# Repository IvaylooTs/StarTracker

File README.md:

# Repo: Star Tracker

**Team Name:** CASSI  
**Project Name:** CASSI (Celestial Alignment System for Satellite Inertial-control)  
**Official Category:** Star Tracker 1

**Team Members:**  
Michael Yan, Ivaylo Tsekov, Alexandra Nedela, Dilyana Vasileva, Tsvetomir Staykov

## Note: for full and final documentation please read Star_Tracker_3.pdf
---

## Problem

How do we determine our attitude in space?

---

## Project Overview and End Goal

This project implements a star tracking system using a **Raspberry Pi** with an **AI camera** to determine the orientation of the system based on captured star images using a deterministic algorithm. Once calibrated, the system works in tandem with an IMU (Inertial Measurement Unit) to track orientation without continuous visual input. When drifting occurs, due to environmental variables, power loss, or other factors, the system automatically recalibrates.

---

## Current Available Demo

Go to the `digital_twin` folder in the `src` directory. It contains:

- `main.py` – main file with all the systems  
- `star_distances_sorted.db` – database with calculated angular distances, sorted in ascending order  
- `star_identified.png` – sample image from previous tests  
- `test_images` – dir with images from *Stellarium* for testing purposes (uses specific resolution and FOV)
- `create_hash.py` - a script to generate a hash map from database table "AngularDistances"
- `catalog_hash.py` - an already generated hash with the script above using 2 degree tolerance
- `stellarium360_new.js` - a script to be pasted into stellarium console for testing purposes
- `script_images` - dir with images generated from the above script

To run the script, you will need the `sqlite3` and `cv2` libraries installed on your system, and Python 3.

To run the script, use:
```bash
python3 main.py 
```

The results in your terminal should be:

- Indicator of which image you are currently processing
- Which mode you're in (Lost-in-Space / Tracking)
- The resulting quaternion from either of the two modes if one is produced
- The mapping of image star to HIP ID if one is produced

Files that should be generated when you run the script:

- For each image that you're processing you should get a file generated in this format "stars_identified_[index]"

---

## System Architecture

### Software

#### Database Structure

We have two tables in our database.  
**Table 1 – "Stars"** contains the HIP of each star according to the Hipparcos catalog, the magnitude of each star, and x, y, z coordinates of a unit vector corresponding to their RA and DEC coordinates in the equatorial coordinate system.  
**Table 2 – "AngularDistances"** contains the calculated angular distance between each pair of stars in Table 1, sorted from lowest to highest value.

The stars are filtered based on:

- Brightness  
- Size  
- Eccentricity

#### Lost-in-Space Algorithm

We're implementing a Lost-in-Space approach based on pair matching. The algorithm has four main parts:  
1. Image Processing and Feature Extraction  
2. Angular Distance Calculations  
3. Mapping to Catalog  
4. Attitude Determination

---

#### 1. Image Processing and Feature Extraction

The stars in the image are filtered based on: Brightness, Size, and Eccentricity.  
Then we select the N brightest stars in our image using blob detection and the `cv2` Python module. From this, we get the (x, y) coordinates of the center of each star in the image.

---

#### 2. Angular Distance Calculations

- We center the (x, y) coordinates of the stars based on our image's center, then convert them into vectors with the focal length as the coordinate along the z-axis  
- Convert them into unit vectors to reduce unnecessary computation  
- Calculate the angular distance between each pair (using the cosine of the dot product of the two vectors)

---

#### 3. Mapping Stars to Catalog 

- For each pair of stars in our image, we get the candidates ID pairs from our catalog hash
- Then we assign the candidate IDs for each image star based on a voting system
- Afterwards we run a DFS on this graph-like structure to find all possible mappings (even if incomplete)
- In the end we score the solutions we got from the DFS to get the best one

---

#### 4. Attitude Determination 

- From the final mapping of each star to a certain HIP in our database (from step above), we can now retrieve unit vectors from **Table 1**  
- We build the attitude profile matrix from the two sets of image and catalog vectors
- We then build the attitude profile matrix in quaternion form 
- We solve for the eigenvector with the largest eigenvalue which corresponds to our orientation quaternion

---

#### Tracking algorithm

- For tracking we use a previous orientation quaternion to predict where the stars in our previous image are going to be in the next one 
based on a certain amount of euclidian distance threshold this way we can make small and fast corrections to. We use the hungarian algorithm

---

### Hardware

#### Hardware Integration

- The initial orientation determined via camera is stored as a reference  
- The IMU is zeroed at this orientation  
- Subsequent orientation tracking is performed using only the IMU until recalibration is required due to drift

Notes and Ideas:
- A simple way to recalibrate would be to do it periodically  
- For improved accuracy, consider using Kalman filtering

---

#### Mechanical Design

- Modular, layered physical design:
  - Raspberry Pi  
  - IMU module  
  - Camera mounted perpendicular to the Raspberry Pi board  

- 3D CAD models and assembly diagrams are available in the `DOCS/` directory

---

##  Current Progress

### Software

- [x] Define project requirements  
- [x] Find algorithm for identification of stars  
- [x] OpenCV star identification on image  
  - [x] Test model with math on hand  
- [x] Get angular distances between stars  
- [x] Create database of parameters for comparison (star 1 HIP, star 2 HIP, angular distance)  
- [x] Select candidates for possible stars in specific locations  
- [x] Identify the correct stars  
- [x] Orientation in quaternion form
- [x] Testing  

### Hardware

- [x] Configure Raspberry Pi  
- [x] Connect required modules  
  - [x] Camera  
  - [x] IMU (Gyroscope, Accelerometer, Magnetometer)  
- [x] Calibrate IMU at hardware level  
  - [x] Measure drift  
  - [x] Research drift correction  
- [x] Calibrate IMU at software level  
- [x] Add interface for communication with Arduino (I2C is a good candidate)  
- [x] Develop firmware  
  - [x] Auto boot configuration  

### CAD

- [x] Construct simple box for fit testing and basic implementation  
- [x] Build a better box for testing and protection  
- [x] Satellite enclosure with removable modules  
  - [x] Bottom panel  
  - [x] Sliders  
  - [x] Test sliders  
  - [x] Side protection panels  
  - [x] CASSI module  

### Additional

- [x] Testing | Make black box for testing using images on a monitor  
- [x] Visualization | Make control panel  
  - [x] 3D visualization  
  - [x] Live video  
  - [x] OpenCV calculations  
  - [x] Control buttons  
- [x] Check if static IP is needed (just in case)  
- [x] Study commercial star tracker manuals  
- [x] Consider handling edge cases such as solar flares, moonlight, sun/earth stray light, etc.

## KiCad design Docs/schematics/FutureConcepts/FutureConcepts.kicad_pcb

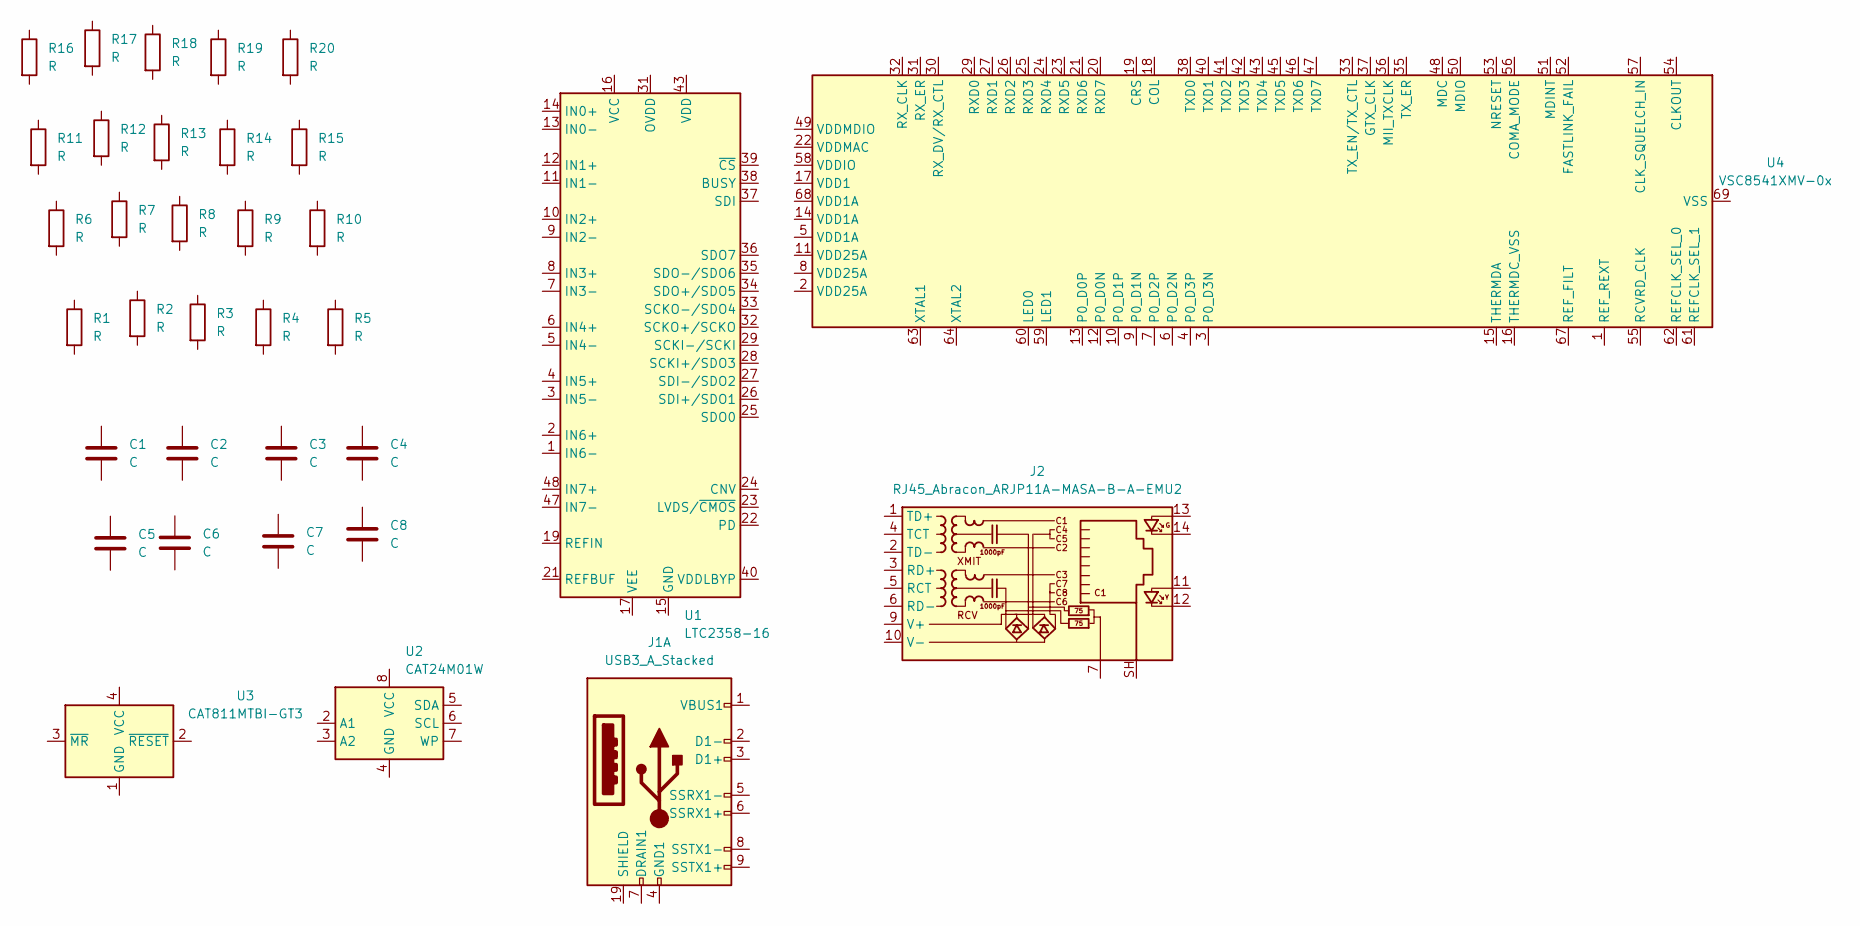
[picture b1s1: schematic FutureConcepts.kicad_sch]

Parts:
C1, C2, C3, C4, C5, C6, C7, C8: C; C_Elec_6.3x5.4
J1: USB3_A_Stacked; USB3_A_Molex_48406-0001_Horizontal_Stacked
J2: RJ45_Abracon_ARJP11A-MASA-B-A-EMU2; RJ45_Abracon_ARJP11A-MA_Horizontal
R1, R2, R3, R4, R5, R6, R7, R8, R9, R10, R11, R12, R13, R14, R15, R16, R17, R18, R19, R20: R; R_2010_5025Metric_Pad1.40x2.65mm_HandSolder
U1: LTC2358-16; LQFP-48_7x7mm_P0.5mm
U2: CAT24M01W; SOIC-8_3.9x4.9mm_P1.27mm
U3: CAT811MTBI-GT3; SOT-143
U4: VSC8541XMV-0x; QFN-68-1EP_8x8mm_P0.4mm_EP5.2x5.2mm

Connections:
unnamed: U1.15 (GND), U1.18 (GND), U1.20 (GND), U1.30 (GND), U1.41 (GND), U1.44 (GND), U1.46 (GND)
unnamed: U1.42 (VDD), U1.43 (VDD)
unnamed: U1.17 (VEE), U1.45 (VEE)
unnamed: U4.17 (VDD1), U4.34 (VDD1)
unnamed: U4.22 (VDDMAC), U4.28 (VDDMAC), U4.39 (VDDMAC), U4.44 (VDDMAC)

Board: 2 copper layers, 35 parts (0 on the bottom side), 5 nets, no tracks yet.

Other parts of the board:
Module1: ComputeModule5-CM5; Raspberry-Pi-5-Compute-Module

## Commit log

2025-07-21 Initial code
2025-07-22 tsetso first commit
2025-07-22 catalog csv
2025-07-22 day 2 update
2025-07-22 bad idea fix
2025-07-22 ssh and changed structure
2025-07-23 localizatior
2025-07-23 day 3
2025-07-24 added db creator+ custom query for deleting and testing, added db
2025-07-24 ☆ star_coords_to_unit_vector and angular_distances functions
    - star_coords_to_unit_vector:
    The function takes the parameters of the camera (center coordinates, focal length) and an array of star coordinates in the image. I then returns a list of unit vectors for each star
    - angular_distances:
    The function takes a list of unit vectors and calculates the angular distances between each pair of stars.
    Returns an array of all of them
    - Also I deleted the two previous digital twins since they were AI and stuff
2025-07-24 sorted
2025-07-24 new sorted
2025-07-24 disctionary
2025-07-24 debugging and fine tuning of angular distances
    kill me, kill me right now
2025-07-25 ☆ some refactoring
2025-07-25 ☆ hypothesises dict construction
    trying to make a graph-like structure in the form of a dict
    Then I'll attempt some sort of graph traversal algorithm + maybe voting algorithm to get final mapping of the stars
    - load_catalog_angular_distances(): query to db to get all pairs of angular distances within a certain tolerance. Probably going to change it to a k-vector
    - display_star_detections(): moved the displaying code to a separate function
    - within_bounds(): calculate min max based on tolerance of the angular distance arg
    - load_hypothesies: returns a dict where the key is the index of the star in our image and the value is a list of all the possible hip id's it could be
2025-07-25 Hardware backup!
2025-07-25 Updated docs;
2025-07-25 Update line error
2025-07-25 added diagram
2025-07-26 ☆ Readme update
2025-07-26 ☆ Readme update + repo structure
2025-07-26 ☆ Another Readme update
2025-07-26 Day 6
2025-07-26 ☆ Refactoring
    - catalog_angular_distances(): returns a dict where the key is a tuple of a pair of the stars in our image and the value is a dict of all candidate pairs in the database and their angular distance
    -image_processing folder: testing other algorithms to get more correct pixel coordinates
2025-07-26 rename
2025-07-27 random
2025-07-27 >> Readme attempt to fix; tracking days progress
2025-07-28 day 8 research
2025-07-29 ☆ correct angular distances + mapping algorithm attempt
    THE FOV IN STELLARIUM IS THE VERTICAL FOV, NOT THE HORIZONTAL ONE >:(
    - DFS: I implemented a DFS-like traversal. On each step I try a potential ID assignment for it then I check if that assignment would be consistent with all the other angular distnaces in the already 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
2025-07-29 ☆ Image triplet hashing
    - triplet_properties(): returns a list of properties for a triplet of stars (sides, area and elongation)
    - is_degenerate_triplet(): checks properties of a triplet to see if it's meaningful
    - hash_key(): generates a key for our hash table: a tuple of the normalized sorted sides of the triplet
    - generate_geometric_hashes(): combines the functions above to generate a dict where the keys are generated by hash_key and the value is the indecies of the stars in the triplet
2025-07-29 ☆ Retrying push
    I don't know why my last two commits didn't change main.py I guess it wasn't selected. Happy my computer didn't crash out
2025-07-29 day 9 research; finish webpage; backup of RPI codes;
2025-07-30 Rename 01 -> some ideas.md to 01_some ideas.md
2025-07-30 update main with new image filter
2025-07-30 return to original main
2025-07-30 ☆ Final mappin (added subgraph scoring)
    - So turns out geometric hashing is still way to slow even when the
    - DFS(): now it adds all possible assignments it's gone through even if they aren't full to the solutions array
    - score_solution(): given a solution the function returns a tuple of the solution and it's score. The score is calculated based on the angular distance offset between image and catalog pair angular d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
    - load_solution_scoring(): returns an array of tuple where each element is the solution and it's score
    !!! It's still a bi
2025-07-30 ☆ QUEST implementation
    !!! Need to add weights for reliability of each mapping of star to hip, so that outliers don't affect our end attitude as much
    - here I assume that all star assignments can be equally trusted
    - also need to optimize dfs
2025-07-30 ui software; current working firmware; research of hardware backup systems; moved old files;
2025-07-30 removed privated keys.. oops..
2025-07-31 ☆ Refactoring
    - tried to sort my hypothesises before DFS to apply a minimum remaining values heuristic, doesn't really make that big of a change though
    - image processing refactoring (Ivo, don't use that much AI, please)
2025-07-31 txt file for UART progress and code in case LOST
2025-07-31 ☆ Lost in space 1st draft documentation
2025-07-31 initial UART done
2025-08-04 ☆ unit vector changes
    - Refactoring + Viktor Danchev style comments
2025-08-04 ☆ Angular distance calculation optimization
    - using matrix multiplication instead of for loops. Time complexity is still O(N^2), but constant factors are reduced. Numpy uses BLAS C interfaces => faster
2025-08-04 ☆ catalog extraction + hypotheses construction
    - query sent to the database only once for the angular distances. Afterwards filtering done in python
2025-08-04 ☆ improvements to DFS logic
    - I'm scared that someone's gonna think the comments are because the code is copy-pasted AI when I write them manually 'cause I like how Viktor Danchev writes his code
2025-08-04 ☆ New image processing module
2025-08-04 Uploaded Documentation
    First documentation draft for CASSI Star Tracker
2025-08-04 Delete Documentation Star Tracker.pdf
    Didn't upload into correct place
2025-08-04 Documentation Star Tracker
    First draft of the documentation of the Star Tracker CASSI
2025-08-04 Create Documentation Star Tracker.pdf
    Uploaded the file into new folder
2025-08-04 Create Documentation_StarTracker
    Created a folder for the documentation of the star tracker
2025-08-04 ☆ Solution scoring refactoring
2025-08-05 ☆ Weighted sum matrix refactoring + explanation comments
2025-08-05 ☆ Digital twin testing images
2025-08-05 new schematics; logo uploaded; some documentation on data; some concept diagrams
2025-08-05 latest developer UI
2025-08-06 ☆ New image processing (refactored) + new test images
    The image processing code is not my own it's Ivo's he just told me to refactor it
2025-08-07 ☆ Hypothesis construction optimization + new testing images
2025-08-07 ☆ Added inverse_rotate_vectors function
2025-08-07 ☆ Add reprojecting catalog vectors to image plane logic
2025-08-07 tune image_processing and add addaptive treshhold for background instead of global
2025-08-07 ☆ Correcting quaternion logic - add calculate_error and calculate_weights function. Manually correcting original quaternion once
2025-08-07 Angular distance attempted fix
2025-08-07 first working demo; some research; website fixes
2025-08-07 math focal length update; possible fix for FOV problem in different scales
2025-08-09 testing images for angles; new UI design; some documentation
2025-08-09 test of subpixel image processing
2025-08-09 ☆ testing images
2025-08-09 ☆ using subpixel accuracy for lost-in-space
2025-08-10 added queries for planets + js script for stellarium image testing
2025-08-10 current working code; quatenrion visualzaiton in interface; bit docs
2025-08-10 deleted older versions of image processing
2025-08-10 fixed main (my bad)
2025-08-11 test images
2025-08-11 change script for stellarium to work in any direction
2025-08-11 ☆ baffle block simulation images
2025-08-11 toggleable objects; readme; star sphere in 3d view; bigger 3d view;
2025-08-11 ☆ Fixing docstrings
    I know this is pointless, don't blame me guys
2025-08-11 ☆ fixed image path
2025-08-11 ☆ Fine-tuning of parameters - lost-in-space big speed-up
2025-08-11 created sales website! fully functional (source: trust me bro)
2025-08-11 moved site
2025-08-12 added potential hash dictionary with voting system for filtering the potential candidates before the DFS
2025-08-12 ☆ tracking functionality first version + testing images
2025-08-12 more speed testing
2025-08-12 Stashing changes to begin tests
2025-08-12 websocket optimizations;
2025-08-13 ☆ testing and refactoring tracking
2025-08-13 ☆ Function to refine quaternion before returning is from lost-in-space
2025-08-13 ☆ Rotational angle between quaternions function
2025-08-13 ☆ testing new error rates and weights functions with radians + rotational angle between quaternions fixed
2025-08-13 added solution for planets in picture - progressive removal of inacurate objects and rerunning the dfs
2025-08-13 add photos
2025-08-14 comment unused stuff
2025-08-14 ☆ Lost-in-Space using testing image if None provided + new testing images
2025-08-15 ☆ Quaternion refinement pipeline upgrade
2025-08-15 ☆ Tracking and unit vector conversion optimisation with vectorised operations
2025-08-15 ☆ Create hash functionality added to main digital twin + generated pickle file
2025-08-15 ☆ Added hypotheses generation for DFS based on catalog hash functions
2025-08-15 ☆ DFS with new hypotheses + tracking changes + testing images
2025-08-16 presentation future concept; beginning of tests ( stashed for testing integration rn)
2025-08-16 documentation; testing scripts; developer ui change display stats; some research paste; some test images;
2025-08-16 ☆ Added planetary exclusion iteration
2025-08-16 ☆ New file structure + star tracker related classes
    !!! Not tested yet !!!
    + haven't written the __init__ files
2025-08-16 documentation; testing lis accuracy
2025-08-16 ☆ lost-in-space testing
    !!! have to fix dir of stars_identified.png
2025-08-17 ☆ Fixed identified stars image output dir
2025-08-17 ☆ Tracking fix parameters passed. Doesn't break
2025-08-17 added sun filter to the thanos gauntlet
2025-08-17 ☆ Hungarian algorithm matching instead of greedy first smallest distance
2025-08-18 ☆ Error handling for unit vectors and angular distances + types
2025-08-18 ☆ Hypotheses building error handling + type hints
2025-08-18 Testing images+ scripts for performance graphs
2025-08-18 change gausian fit with weighted centroids
2025-08-18 ☆ Fixed tracking solution indexation and added new returns to track function + DFS error handling + new testing images
2025-08-18 rework batch validation
2025-08-18 ☆ Modes + loop through multiple images with tracking
2025-08-19 ☆ More testing of tracking
2025-08-20 test/lostinspace.py
2025-08-20 ☆ testing images + clean version update
2025-08-21 ☆ README update + testing images
2025-08-26 backup of source code; final developer UI
2025-10-07 The final and fully completed documentation for this project
